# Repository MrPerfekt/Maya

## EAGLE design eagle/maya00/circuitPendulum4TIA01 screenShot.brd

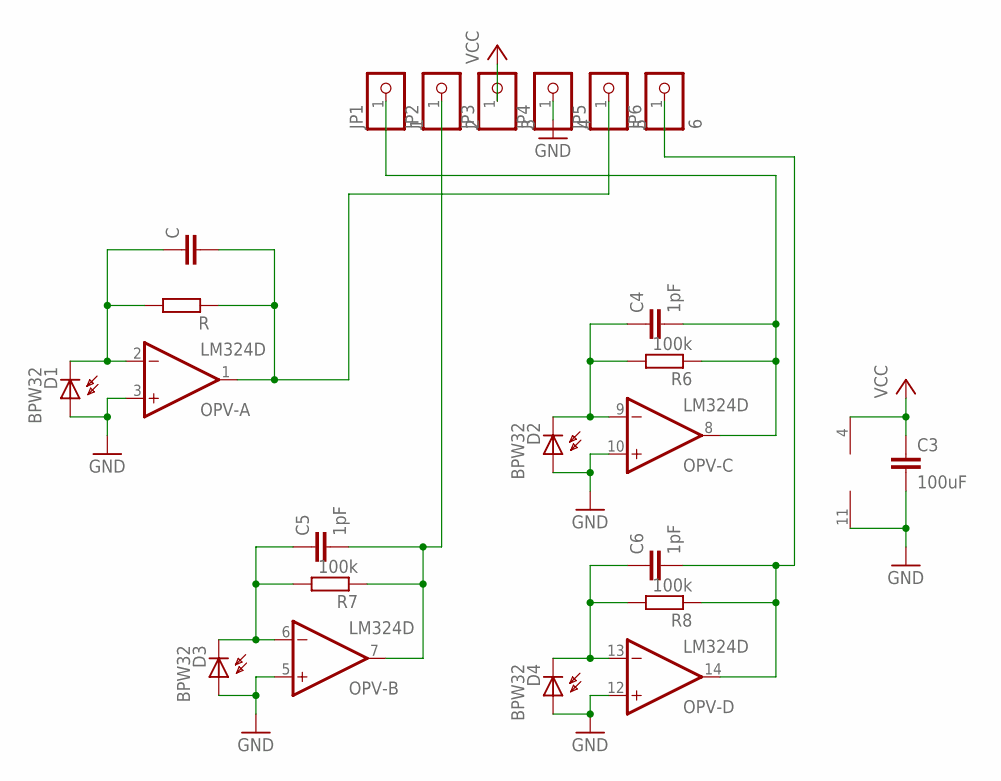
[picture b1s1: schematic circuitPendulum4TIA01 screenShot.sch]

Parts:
C: C-EUC0603; C0603
C3: 100uF; C0603
C4, C5, C6: 1pF; C0603
D1, D2, D3, D4: BPW32
JP1: 1; 1X01SMD
JP2: 2; 1X01SMD
JP3: 3; 1X01SMD
JP4: 4; 1X01SMD
JP5: 5; 1X01SMD
JP6: 6; 1X01SMD
OPV-: LM324D; SO14
R: R-EU_R0603; R0603
R6, R7, R8: 100k; R0603

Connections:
GND: C3.2, D1.A, D2.A, D3.A, D4.A, JP4.1, OPV-.3 (+IN), OPV-.5 (+IN), OPV-.10 (+IN), OPV-.11 (V-), OPV-.12 (+IN)
unnamed: C.2, JP5.1, OPV-.1 (OUT), R.1
unnamed: C4.2, JP1.1, OPV-.8 (OUT), R6.1
unnamed: C.1, D1.K (C), OPV-.2 (-IN), R.2
unnamed: C5.1, D3.K (C), OPV-.6 (-IN), R7.2
unnamed: C5.2, JP2.1, OPV-.7 (OUT), R7.1
unnamed: C6.2, JP6.1, OPV-.14 (OUT), R8.1
unnamed: C6.1, D4.K (C), OPV-.13 (-IN), R8.2
unnamed: C4.1, D2.K (C), OPV-.9 (-IN), R6.2
VCC: C3.1, JP3.1, OPV-.4 (V+)

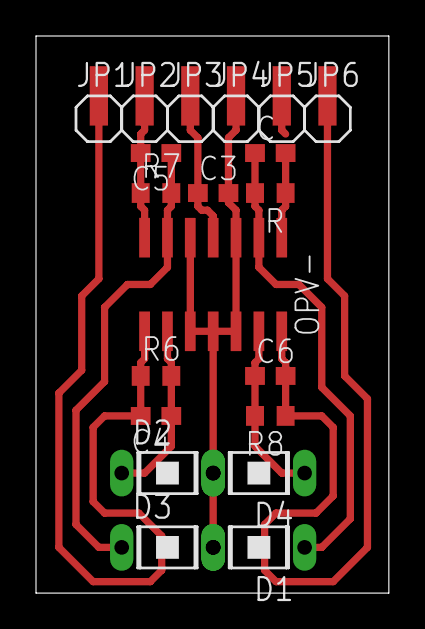
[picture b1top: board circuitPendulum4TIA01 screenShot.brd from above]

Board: 2 copper layers, 19.6 x 30.9 mm, 20 parts (0 on the bottom side), 10 nets.

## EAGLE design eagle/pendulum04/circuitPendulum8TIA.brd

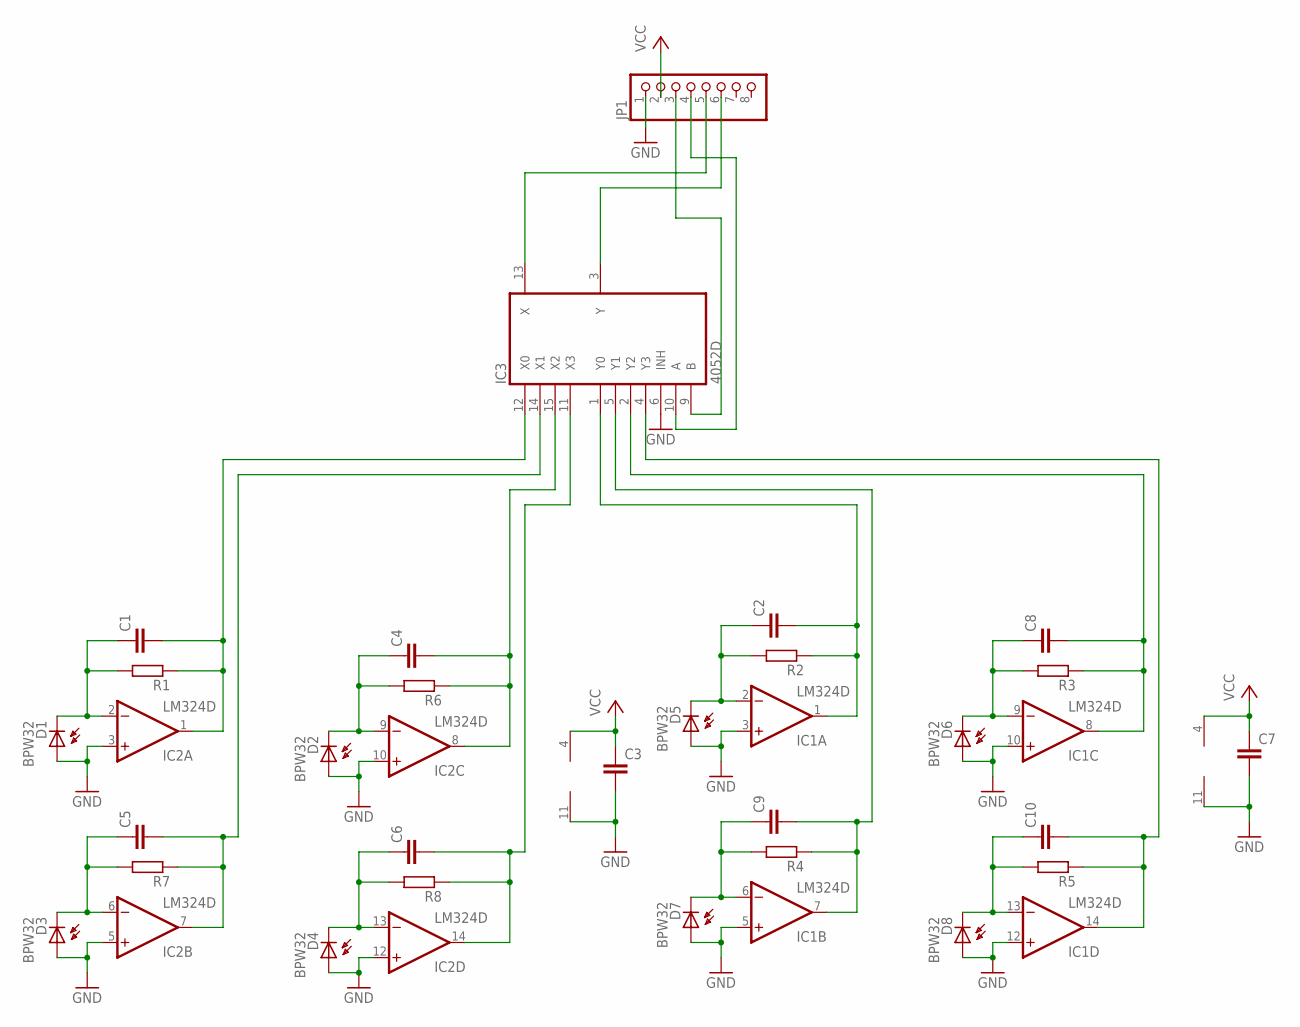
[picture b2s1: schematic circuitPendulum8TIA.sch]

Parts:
C1, C2, C3, C4, C5, C6, C7, C8, C9, C10: C-EUC0603; C0603
D1, D2, D3, D4, D5, D6, D7, D8: BPW32
IC1, IC2: LM324D; SO14
IC3: 4052D; SO16
JP1: PINHD-1X8_2.54; 1X08
R1, R2, R3, R4, R5, R6, R7, R8: R-EU_R0603; R0603

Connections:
GND: C3.2, C7.2, D1.A, D2.A, D3.A, D4.A, D5.A, D6.A, D7.A, D8.A, IC1.3 (+IN), IC1.5 (+IN), IC1.10 (+IN), IC1.11 (V-), IC1.12 (+IN), IC2.3 (+IN), IC2.5 (+IN), IC2.10 (+IN), IC2.11 (V-), IC2.12 (+IN), IC3.6 (INH), IC3.8 (GND), JP1.1
unnamed: C2.1, D5.K (C), IC1.2 (-IN), R2.2
unnamed: C2.2, IC1.1 (OUT), IC3.1 (Y0), R2.1
unnamed: C8.2, IC1.8 (OUT), IC3.2 (Y2), R3.1
unnamed: C9.1, D7.K (C), IC1.6 (-IN), R4.2
unnamed: C9.2, IC1.7 (OUT), IC3.5 (Y1), R4.1
unnamed: C10.2, IC1.14 (OUT), IC3.4 (Y3), R5.1
unnamed: C4.2, IC2.8 (OUT), IC3.15 (X2), R6.1
unnamed: C1.1, D1.K (C), IC2.2 (-IN), R1.2
unnamed: C5.1, D3.K (C), IC2.6 (-IN), R7.2
unnamed: C5.2, IC2.7 (OUT), IC3.14 (X1), R7.1
unnamed: C1.2, IC2.1 (OUT), IC3.12 (X0), R1.1
unnamed: C6.2, IC2.14 (OUT), IC3.11 (X3), R8.1
unnamed: C6.1, D4.K (C), IC2.13 (-IN), R8.2
unnamed: C4.1, D2.K (C), IC2.9 (-IN), R6.2
unnamed: C10.1, D8.K (C), IC1.13 (-IN), R5.2
unnamed: C8.1, D6.K (C), IC1.9 (-IN), R3.2
unnamed: IC3.13 (X), JP1.5
unnamed: IC3.3 (Y), JP1.6
unnamed: IC3.10 (A), JP1.4
unnamed: IC3.9 (B), JP1.3
VCC: C3.1, C7.1, IC1.4 (V+), IC2.4 (V+), IC3.16 (VCC), JP1.2
VEE: IC3.7 (VEE)

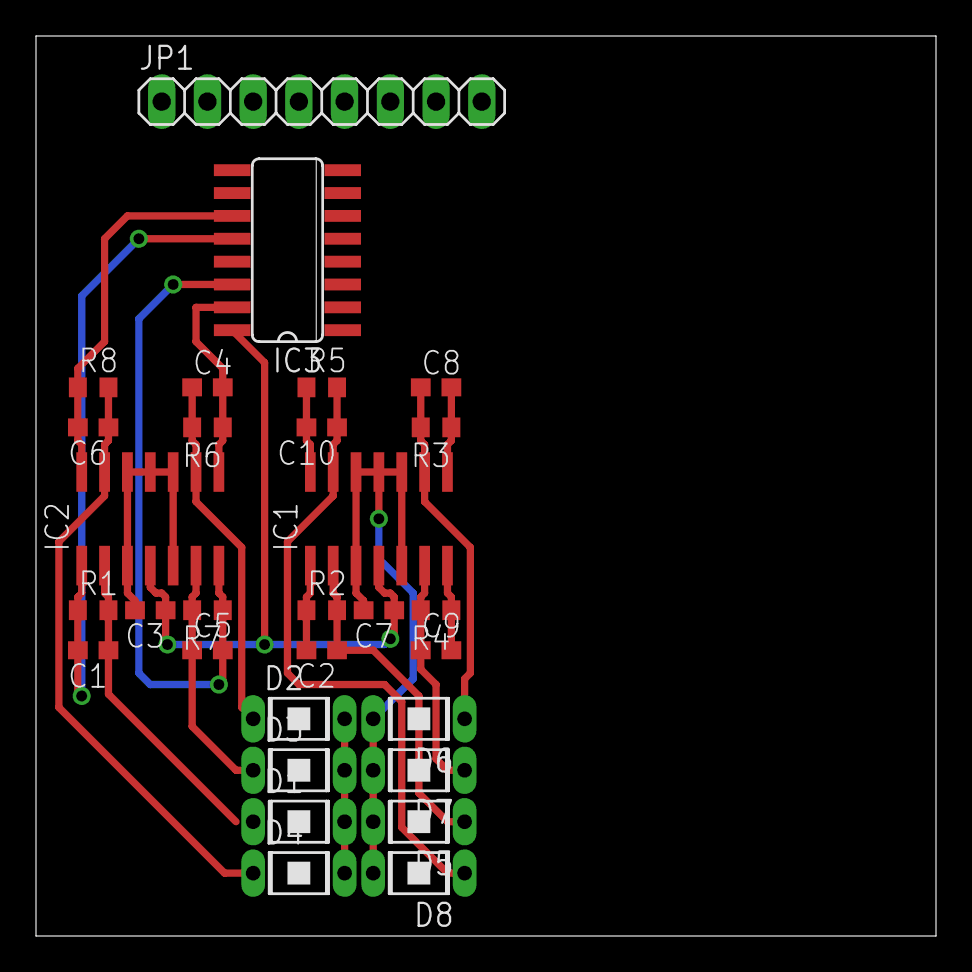
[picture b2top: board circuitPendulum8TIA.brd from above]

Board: 2 copper layers, 50.0 x 50.0 mm, 30 parts (0 on the bottom side), 22 nets.

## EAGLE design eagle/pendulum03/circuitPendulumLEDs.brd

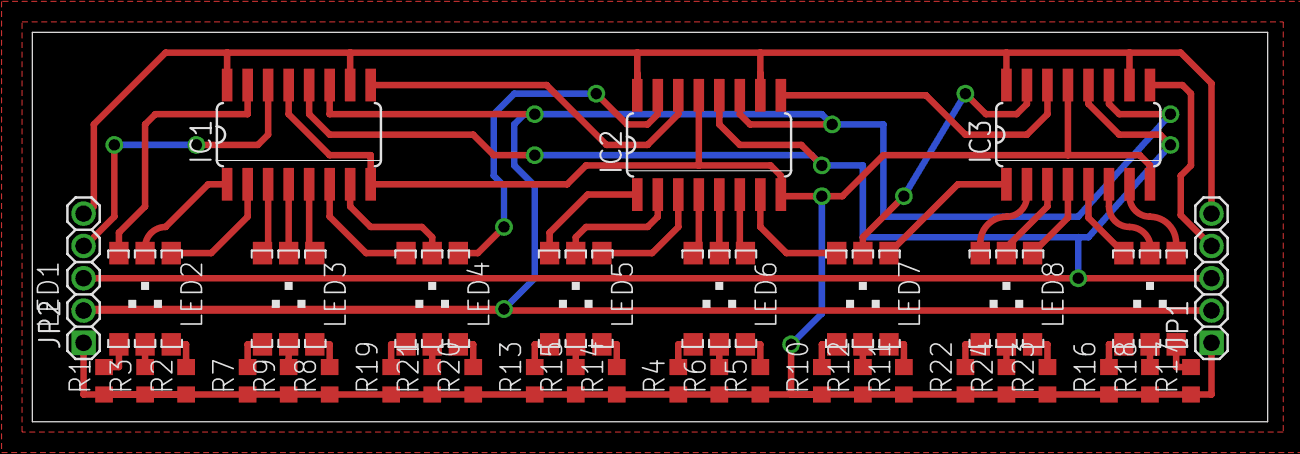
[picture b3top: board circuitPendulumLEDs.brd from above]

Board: 2 copper layers, 76.5 x 24.1 mm, 37 parts (0 on the bottom side), 56 nets.

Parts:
IC1, IC2, IC3: 74HC595D; SO16
JP1: Out; 1_05X2MM
JP2: In; 1_05X2MM
LED1, LED2, LED3, LED4, LED5, LED6, LED7, LED8: 20mA; PLCC-6_SAMSUNG
R1, R2, R3, R4, R5, R6, R7, R8, R9, R10, R11, R12, R13, R14, R15, R16, R17, R18, R19, R20, R21, R22, R23, R24: R0603

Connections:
GND: IC1.8, IC1.13, IC2.8, IC2.13, IC3.8, IC3.13, JP1.1, JP2.1, R1.1, R2.1, R3.1, R4.1, R5.1, R6.1, R7.1, R8.1, R9.1, R10.1, R11.1, R12.1, R13.1, R14.1, R15.1, R16.1, R17.1, R18.1, R19.1, R20.1, R21.1, R22.1, R23.1, R24.1
L1B: IC1.2, LED1.3
L1G: IC1.1, LED1.2
L1R: IC1.15, LED1.1
L2B: IC1.5, LED2.3
L2G: IC1.4, LED2.2
L2R: IC1.3, LED2.1
L3B: IC2.15, LED3.3
L3G: IC1.7, LED3.2
L3R: IC1.6, LED3.1
L4B: IC2.3, LED4.3
L4G: IC2.2, LED4.2
L4R: IC2.1, LED4.1
L5B: IC2.6, LED5.3
L5G: IC2.5, LED5.2
L5R: IC2.4, LED5.1
L6B: IC3.1, LED6.3
L6G: IC3.15, LED6.2
L6R: IC2.7, LED6.1
L7B: IC3.4, LED7.3
L7G: IC3.3, LED7.2
L7R: IC3.2, LED7.1
L8B: IC3.7, LED8.3
L8G: IC3.6, LED8.2
L8R: IC3.5, LED8.1
unnamed: LED1.4, R1.2
unnamed: LED1.6, R2.2
unnamed: LED1.5, R3.2
unnamed: LED5.4, R4.2
unnamed: LED5.6, R5.2
unnamed: LED5.5, R6.2
unnamed: LED4.4, R13.2
unnamed: IC1.9, IC2.14
unnamed: LED4.6, R14.2
unnamed: LED4.5, R15.2
unnamed: LED8.4, R16.2
unnamed: LED8.6, R17.2
unnamed: IC1.14, JP2.4
unnamed: IC2.9, IC3.14
unnamed: LED8.5, R18.2
unnamed: LED6.4, R10.2
unnamed: LED6.6, R11.2
unnamed: LED6.5, R12.2
unnamed: LED2.4, R7.2
unnamed: IC3.9, JP1.4
unnamed: LED2.6, R8.2
unnamed: IC1.12, IC2.12, IC3.12, JP1.2, JP2.2
unnamed: LED2.5, R9.2
unnamed: IC1.11, IC2.11, IC3.11, JP1.3, JP2.3
unnamed: LED3.4, R19.2
unnamed: LED3.6, R20.2
unnamed: LED3.5, R21.2
unnamed: LED7.4, R22.2
unnamed: LED7.6, R23.2
unnamed: LED7.5, R24.2
VCC: IC1.10, IC1.16, IC2.10, IC2.16, IC3.10, IC3.16, JP1.5, JP2.5

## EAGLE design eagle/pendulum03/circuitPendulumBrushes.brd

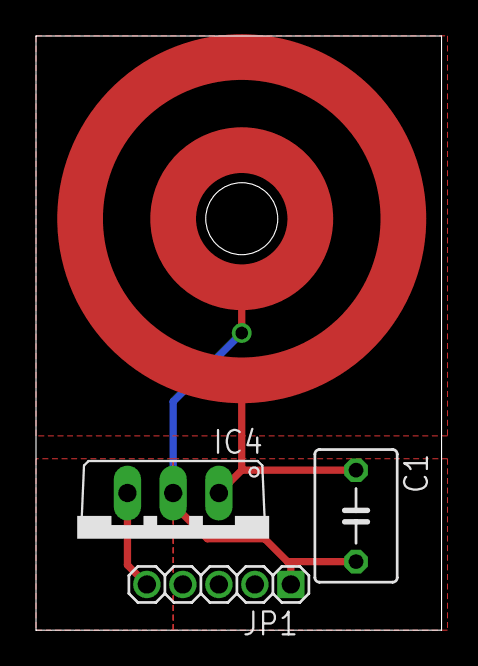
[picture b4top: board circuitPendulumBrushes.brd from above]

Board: 2 copper layers, 22.5 x 33.0 mm, 3 parts (0 on the bottom side), 3 nets.

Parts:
C1: 100uF; C050-045X075
IC4: 786TV; TO220V
JP1: Out; 1_05X2MM

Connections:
GND: C1.2, IC4.2, JP1.1
VCC: IC4.3, JP1.5
VIN: C1.1, IC4.1

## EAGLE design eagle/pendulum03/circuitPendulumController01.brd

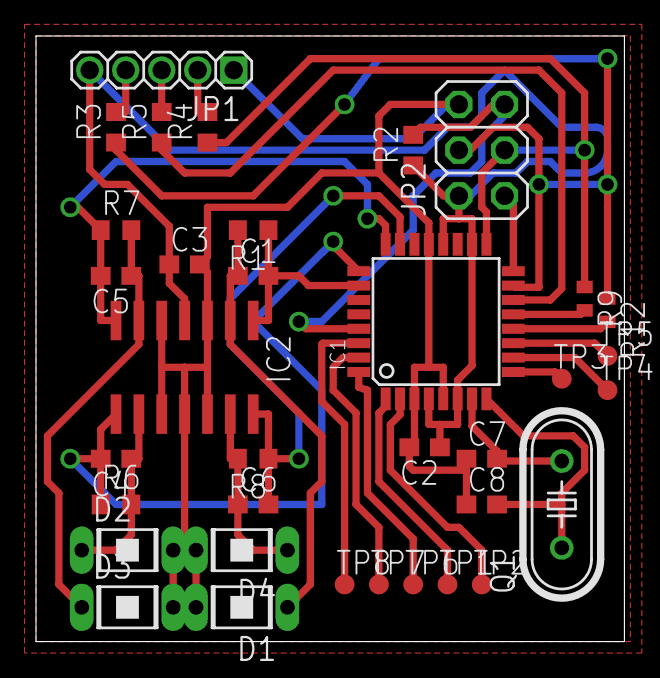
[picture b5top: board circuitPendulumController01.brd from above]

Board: 2 copper layers, 32.7 x 33.6 mm, 35 parts (0 on the bottom side), 30 nets.

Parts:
C1, C4, C5, C6: 10pF; C0603
C2, C3: 100nF; C0603
C7, C8: 22pF; C0603
D1, D2, D3, D4: BPW32
IC1: MEGA8-AI; TQFP32-08
IC2: LM324D; SO14
JP1: Out; 1_05X2MM
JP2: ICSP; 2X03
Q1: 16MHz; HC49/S
R1, R6, R7, R8: 1MOhm; R0603
R2: 10kOhm; R0603
R3, R4, R5: 100Ohm; R0603
R9: JP1; R0402
R12: JP2; R0402
TP1, TP2, TP3, TP4, TP5, TP6, TP7, TP8: TPTP11R; TP11R

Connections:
GND: C2.2, C3.2, C7.1, C8.1, D1.A, D2.A, D3.A, D4.A, IC1.3, IC1.5, IC1.21, IC2.3, IC2.5, IC2.10, IC2.11, IC2.12, JP1.1, JP2.6
MISO: IC1.16, JP2.1
MOSI: IC1.15, JP2.4, R3.1, R12.1
unnamed: IC1.12, R12.2
unnamed: IC1.13, R9.2
unnamed: IC1.14, R5.1
unnamed: C4.2, IC1.25, IC2.8, R6.1
unnamed: C1.1, D1.K, IC2.2, R1.2
unnamed: C5.1, D3.K, IC2.6, R7.2
unnamed: C5.2, IC1.24, IC2.7, R7.1
unnamed: C1.2, IC1.26, IC2.1, R1.1
unnamed: C6.2, IC1.23, IC2.14, R8.1
unnamed: C6.1, D4.K, IC2.13, R8.2
unnamed: C4.1, D2.K, IC2.9, R6.2
unnamed: C7.2, IC1.7, Q1.2
unnamed: C8.2, IC1.8, Q1.1
unnamed: IC1.1, TP1.TP
unnamed: IC1.2, TP2.TP
unnamed: IC1.9, TP3.TP
unnamed: IC1.10, TP4.TP
unnamed: IC1.11, TP5.TP
unnamed: IC1.32, TP6.TP
unnamed: IC1.31, TP7.TP
unnamed: IC1.30, TP8.TP
RCK_OUT: JP1.2, R5.2
RST: IC1.29, JP2.5, R2.2
SCK: IC1.17, JP2.3, R4.1, R9.1
SCK_OUT: JP1.3, R4.2
SER_OUT: JP1.4, R3.2
VCC: C2.1, C3.1, IC1.4, IC1.6, IC1.18, IC1.20, IC2.4, JP1.5, JP2.2, R2.1

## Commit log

2017-01-21 Add files
